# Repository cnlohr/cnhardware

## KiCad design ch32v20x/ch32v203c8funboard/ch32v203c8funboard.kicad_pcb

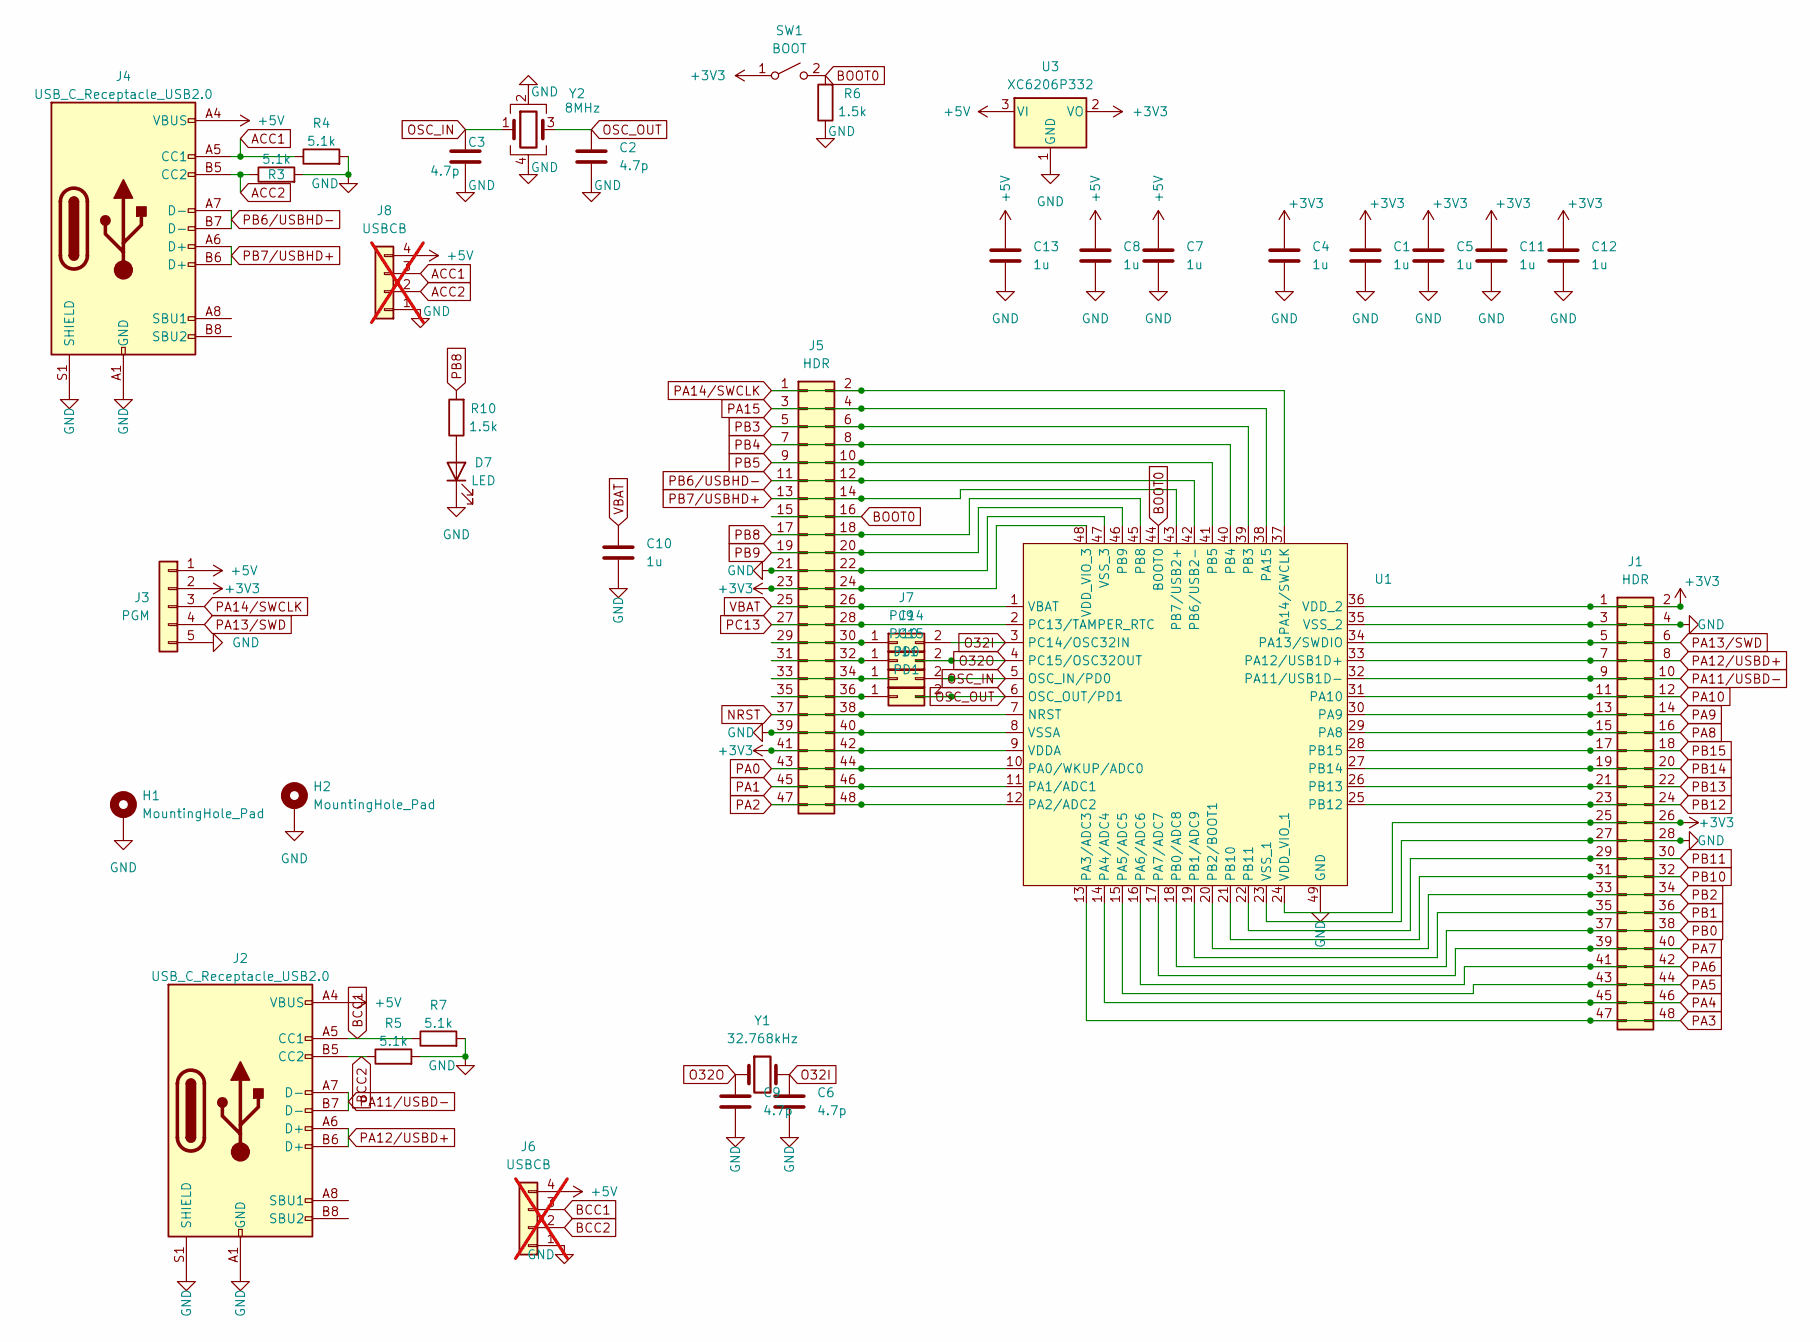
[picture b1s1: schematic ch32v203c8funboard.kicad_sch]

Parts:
C1, C4, C5, C7, C8, C10, C11, C12, C13: 1u; C_0402_1005Metric; LCSC C52923
C2, C3, C6, C9: 4.7p; C_0402_1005Metric; LCSC C325453
D7: LED; LED_0402_1005Metric; LCSC C74342
H1, H2: MountingHole_Pad; MountingHole_3.2mm_M3_DIN965_Pad
J1, J5: HDR; PinHeader_2x24_P2.54mm_Vertical; LCSC C725896
J2, J4: USB_C_Receptacle_USB2.0; USB_C_Receptacle_HRO_TYPE-C-31-M-12; LCSC C2765186
J3: PGM; PinHeader_1x05_P2.54mm_Vertical; LCSC C492404
J6, J8: USBCB; PinHeader_1x04_P2.54mm_Vertical; not fitted
J7: PC14; SolderJumper-2_P1.3mm_Open_RoundedPad1.0x1.5mm
J9: PC15; SolderJumper-2_P1.3mm_Open_RoundedPad1.0x1.5mm
J10: PD0; SolderJumper-2_P1.3mm_Open_RoundedPad1.0x1.5mm
J11: PD1; SolderJumper-2_P1.3mm_Open_RoundedPad1.0x1.5mm
R3, R4, R5, R7: 5.1k; R_0402_1005Metric; LCSC C25905
R6, R10: 1.5k; R_0402_1005Metric; LCSC C25867
SW1: BOOT; TS-1187A-B-A-B-TACTILE; LCSC C318884
U1: QFN-48-1EP_7x7mm_P0.5mm_EP5.6x5.6mm; LCSC C6407762
U3: XC6206P332; SOT-23; LCSC C5446
Y1: 32.768kHz; Crystal_SMD_3215-2Pin_3.2x1.5mm; LCSC C19076879
Y2: 8MHz; Crystal_SMD_3225-4Pin_3.2x2.5mm; LCSC C400090

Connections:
+3V3: C1.1, C4.1, C5.1, C11.1, C12.1, J1.1, J1.2, J1.25, J1.26, J3.2, J5.23, J5.24, J5.41, J5.42, SW1.1 (A), U1.9 (VDDA), U1.24 (VDD_VIO_1), U1.36 (VDD_2), U1.48 (VDD_VIO_3), U3.2 (VO)
+5V: C7.1, C8.1, C13.1, J2.A4 (VBUS), J2.A9 (VBUS), J2.B4 (VBUS), J2.B9 (VBUS), J3.1, J4.A4 (VBUS), J4.A9 (VBUS), J4.B4 (VBUS), J4.B9 (VBUS), J6.4, J8.4, U3.3 (VI)
ACC1: J4.A5 (CC1), J8.3, R4.1
ACC2: J4.B5 (CC2), J8.2, R3.1
BCC1: J2.A5 (CC1), J6.3, R7.1
BCC2: J2.B5 (CC2), J6.2, R5.1
BOOT0: J5.15, J5.16, R6.2, SW1.2 (B), U1.44 (BOOT0)
GND: C1.2, C2.2, C3.2, C4.2, C5.2, C6.2, C7.2, C8.2, C9.2, C10.2, C11.2, C12.2, C13.2, D7.1 (K), H1.1, H2.1, J1.3, J1.4, J1.27, J1.28, J2.A1 (GND), J2.A12 (GND), J2.B1 (GND), J2.B12 (GND), J2.S1 (SHIELD), J3.5, J4.A1 (GND), J4.A12 (GND), J4.B1 (GND), J4.B12 (GND), J4.S1 (SHIELD), J5.21, J5.22, J5.39, J5.40, J6.1, J8.1, R3.2, R4.2, R5.2, R6.1, R7.2, U1.8 (VSSA), U1.23 (VSS_1), U1.35 (VSS_2), U1.47 (VSS_3), U1.49 (GND), U3.1 (GND), Y2.2, Y2.4
NRST: J5.37, J5.38, U1.7 (NRST)
unnamed: D7.2 (A), R10.1
unnamed: J5.29, J5.30, J7.1
unnamed: J5.31, J5.32, J9.1
unnamed: J5.33, J5.34, J10.1
unnamed: J5.35, J5.36, J11.1
O32I: C6.1, J7.2, U1.3 (PC14/OSC32IN), Y1.2
O32O: C9.1, J9.2, U1.4 (PC15/OSC32OUT), Y1.1
OSC_IN: C3.1, J10.2, U1.5 (OSC_IN/PD0), Y2.1
OSC_OUT: C2.1, J11.2, U1.6 (OSC_OUT/PD1), Y2.3
PA0: J5.43, J5.44, U1.10 (PA0/WKUP/ADC0)
PA1: J5.45, J5.46, U1.11 (PA1/ADC1)
PA2: J5.47, J5.48, U1.12 (PA2/ADC2)
PA3: J1.47, J1.48, U1.13 (PA3/ADC3)
PA4: J1.45, J1.46, U1.14 (PA4/ADC4)
PA5: J1.43, J1.44, U1.15 (PA5/ADC5)
PA6: J1.41, J1.42, U1.16 (PA6/ADC6)
PA7: J1.39, J1.40, U1.17 (PA7/ADC7)
PA8: J1.15, J1.16, U1.29 (PA8)
PA9: J1.13, J1.14, U1.30 (PA9)
PA10: J1.11, J1.12, U1.31 (PA10)
PA11/USBD-: J1.9, J1.10, J2.A7 (D-), J2.B7 (D-), U1.32 (PA11/USB1D-)
PA12/USBD+: J1.7, J1.8, J2.A6 (D+), J2.B6 (D+), U1.33 (PA12/USB1D+)
PA13/SWD: J1.5, J1.6, J3.4, U1.34 (PA13/SWDIO)
PA14/SWCLK: J3.3, J5.1, J5.2, U1.37 (PA14/SWCLK)
PA15: J5.3, J5.4, U1.38 (PA15)
PB0: J1.37, J1.38, U1.18 (PB0/ADC8)
PB1: J1.35, J1.36, U1.19 (PB1/ADC9)
PB2: J1.33, J1.34, U1.20 (PB2/BOOT1)
PB3: J5.5, J5.6, U1.39 (PB3)
PB4: J5.7, J5.8, U1.40 (PB4)
PB5: J5.9, J5.10, U1.41 (PB5)
PB6/USBHD-: J4.A7 (D-), J4.B7 (D-), J5.11, J5.12, U1.42 (PB6/USB2-)
PB7/USBHD+: J4.A6 (D+), J4.B6 (D+), J5.13, J5.14, U1.43 (PB7/USB2+)
PB8: J5.17, J5.18, R10.2, U1.45 (PB8)
PB9: J5.19, J5.20, U1.46 (PB9)
PB10: J1.31, J1.32, U1.21 (PB10)
PB11: J1.29, J1.30, U1.22 (PB11)
PB12: J1.23, J1.24, U1.25 (PB12)
PB13: J1.21, J1.22, U1.26 (PB13)
PB14: J1.19, J1.20, U1.27 (PB14)
PB15: J1.17, J1.18, U1.28 (PB15)
PC13: J5.27, J5.28, U1.2 (PC13/TAMPER_RTC)
VBAT: C10.1, J5.25, J5.26, U1.1 (VBAT)

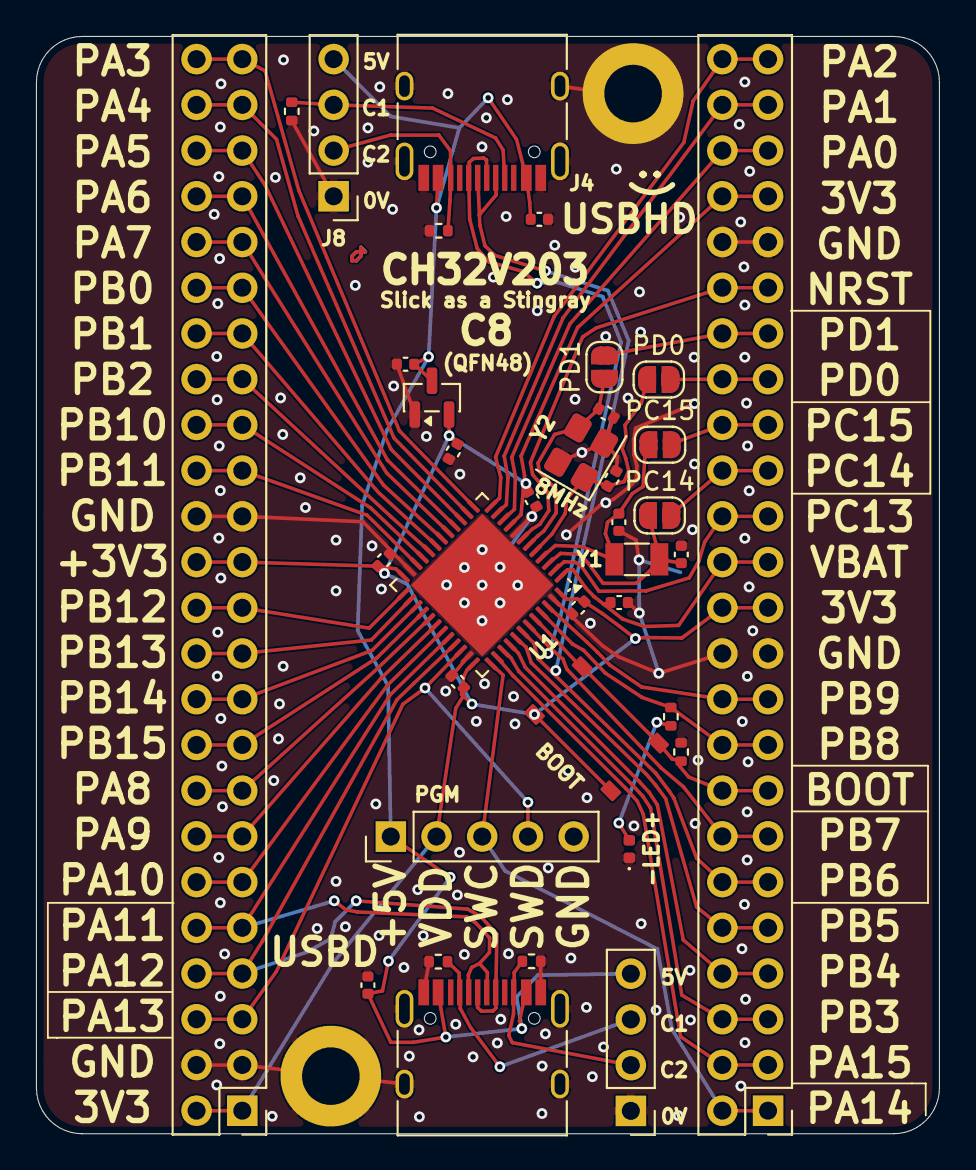
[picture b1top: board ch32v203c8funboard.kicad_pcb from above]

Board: 2 copper layers, 50.2 x 61.0 mm, 38 parts (0 on the bottom side), 52 nets.

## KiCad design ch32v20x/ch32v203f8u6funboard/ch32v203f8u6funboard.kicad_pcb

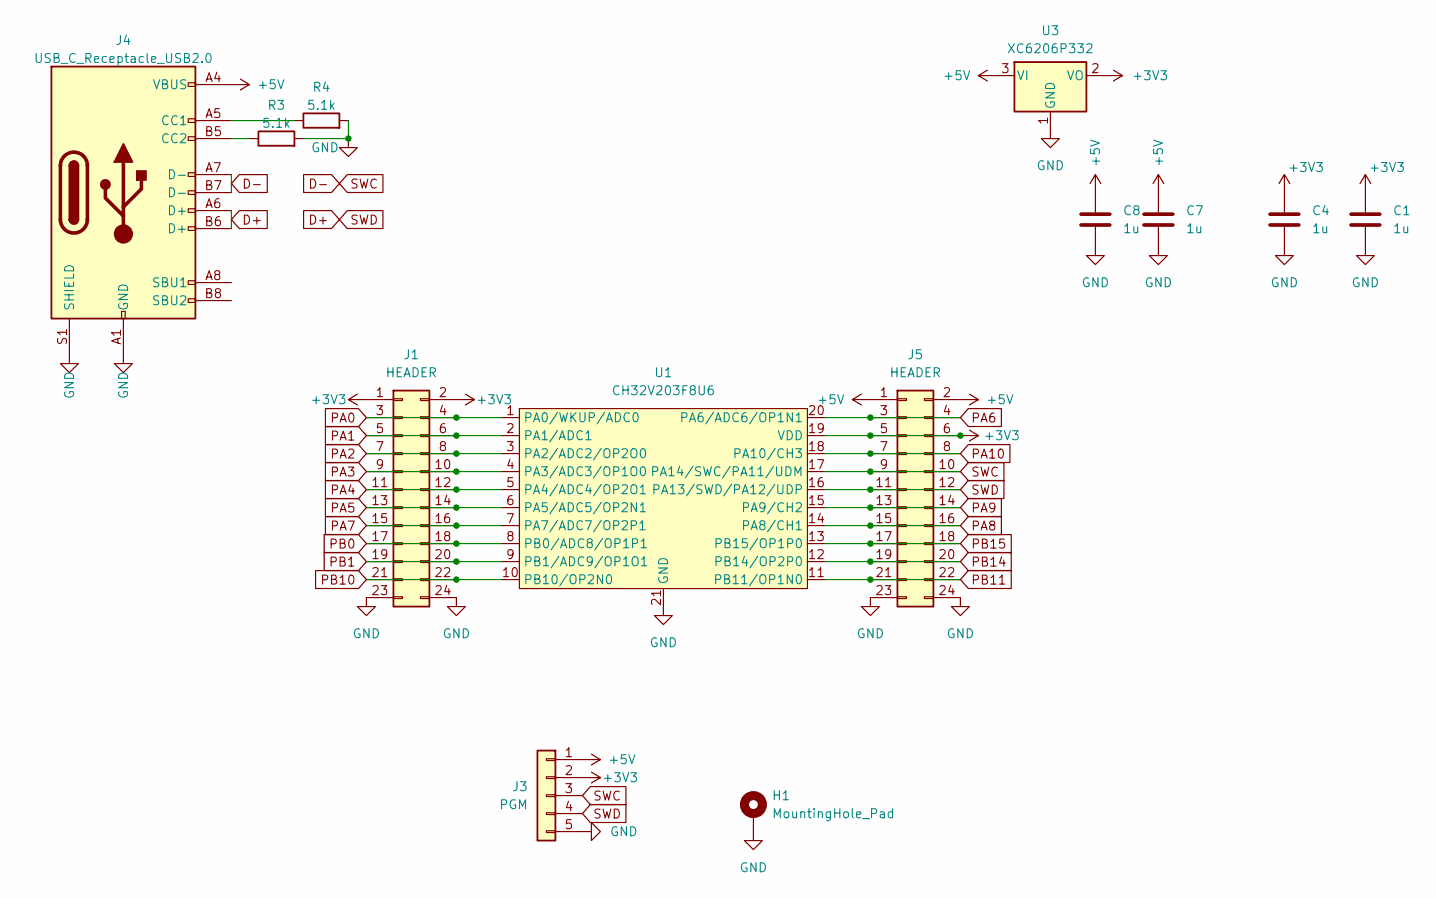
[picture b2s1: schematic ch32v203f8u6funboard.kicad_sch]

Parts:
C1, C4, C7, C8: 1u; C_0402_1005Metric; LCSC C52923
H1: MountingHole_Pad; MountingHole_3.2mm_M3_DIN965_Pad
J1, J5: HEADER; PinHeader_2x12_P2.54mm_Vertical; LCSC C492429
J3: PGM; PinHeader_1x05_P2.54mm_Vertical; LCSC C492404
J4: USB_C_Receptacle_USB2.0; USB_C_Receptacle_HRO_TYPE-C-31-M-12; LCSC C2765186
R3, R4: 5.1k; R_0402_1005Metric; LCSC C25905
U1: CH32V203F8U6; QFN-20-1EP_3x3mm_P0.4mm_EP1.65x1.65mm; LCSC C7570477
U3: XC6206P332; SOT-23; LCSC C5446

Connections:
+3V3: C1.1, C4.1, J1.1, J1.2, J3.2, J5.5, J5.6, U1.19 (VDD), U3.2 (VO)
+5V: C7.1, C8.1, J3.1, J4.A4 (VBUS), J4.A9 (VBUS), J4.B4 (VBUS), J4.B9 (VBUS), J5.1, J5.2, U3.3 (VI)
D+: J3.4, J4.A6 (D+), J4.B6 (D+), J5.11, J5.12, U1.16 (PA13/SWD/PA12/UDP)
D-: J3.3, J4.A7 (D-), J4.B7 (D-), J5.9, J5.10, U1.17 (PA14/SWC/PA11/UDM)
GND: C1.2, C4.2, C7.2, C8.2, H1.1, J1.23, J1.24, J3.5, J4.A1 (GND), J4.A12 (GND), J4.B1 (GND), J4.B12 (GND), J4.S1 (SHIELD), J5.23, J5.24, R3.2, R4.2, U1.21 (GND), U3.1 (GND)
unnamed: J4.A5 (CC1), R4.1
unnamed: J4.B5 (CC2), R3.1
PA0: J1.3, J1.4, U1.1 (PA0/WKUP/ADC0)
PA1: J1.5, J1.6, U1.2 (PA1/ADC1)
PA2: J1.7, J1.8, U1.3 (PA2/ADC2/OP2O0)
PA3: J1.9, J1.10, U1.4 (PA3/ADC3/OP1O0)
PA4: J1.11, J1.12, U1.5 (PA4/ADC4/OP2O1)
PA5: J1.13, J1.14, U1.6 (PA5/ADC5/OP2N1)
PA6: J5.3, J5.4, U1.20 (PA6/ADC6/OP1N1)
PA7: J1.15, J1.16, U1.7 (PA7/ADC7/OP2P1)
PA8: J5.15, J5.16, U1.14 (PA8/CH1)
PA9: J5.13, J5.14, U1.15 (PA9/CH2)
PA10: J5.7, J5.8, U1.18 (PA10/CH3)
PB0: J1.17, J1.18, U1.8 (PB0/ADC8/OP1P1)
PB1: J1.19, J1.20, U1.9 (PB1/ADC9/OP1O1)
PB10: J1.21, J1.22, U1.10 (PB10/OP2N0)
PB11: J5.21, J5.22, U1.11 (PB11/OP1N0)
PB14: J5.19, J5.20, U1.12 (PB14/OP2P0)
PB15: J5.17, J5.18, U1.13 (PB15/OP1P0)

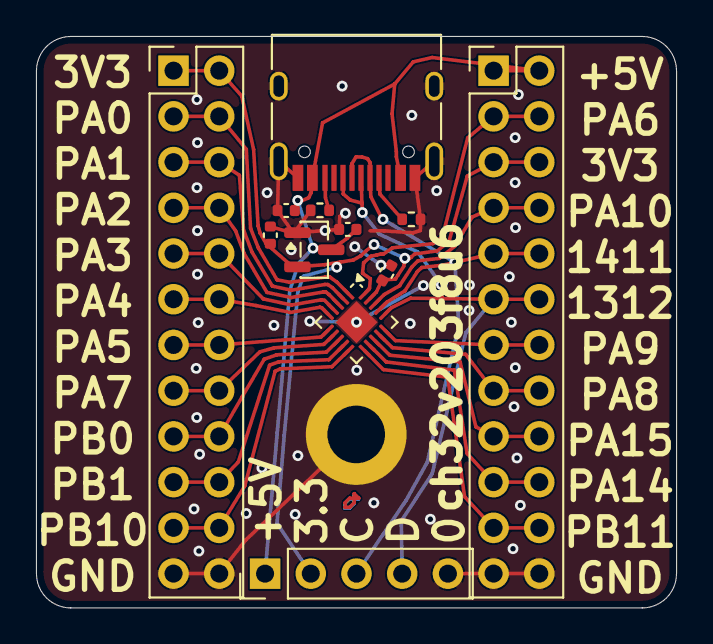
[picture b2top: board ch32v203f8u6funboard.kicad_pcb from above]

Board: 2 copper layers, 35.6 x 31.8 mm, 13 parts (0 on the bottom side), 24 nets.

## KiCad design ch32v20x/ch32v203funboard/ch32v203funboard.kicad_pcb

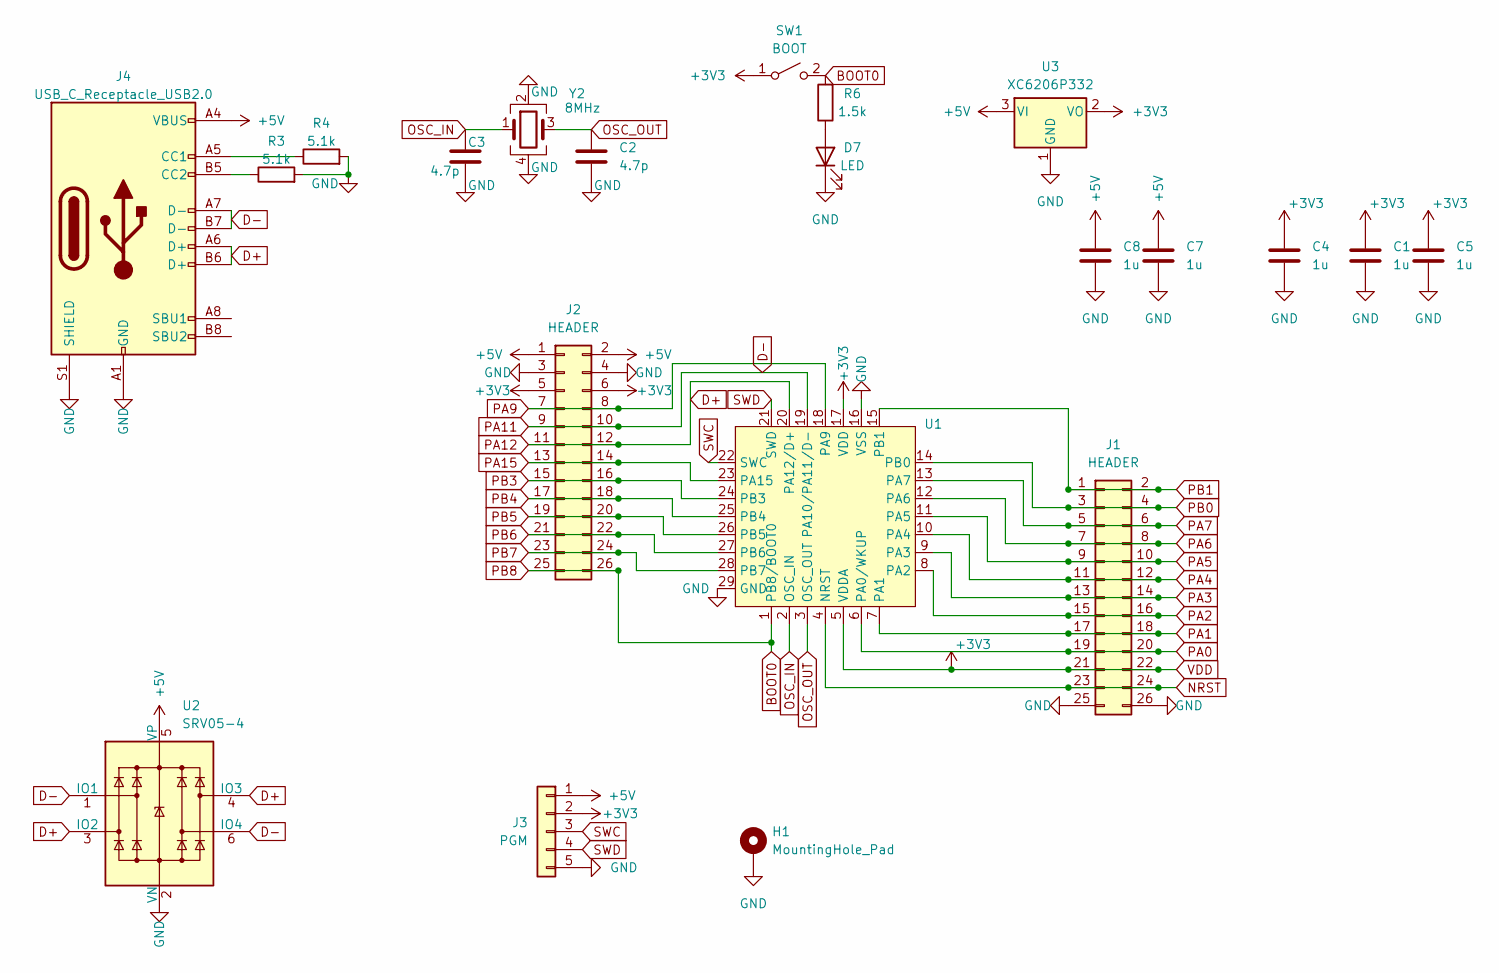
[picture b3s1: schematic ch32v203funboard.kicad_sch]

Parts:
C1, C4, C5, C7, C8: 1u; C_0402_1005Metric; LCSC C52923
C2, C3: 4.7p; C_0402_1005Metric; LCSC C325453
D7: LED; LED_0402_1005Metric; LCSC C74342
H1: MountingHole_Pad; MountingHole_3.2mm_M3_DIN965_Pad
J1, J2: HEADER; PinHeader_2x13_P2.54mm_Vertical; LCSC C358701
J3: PGM; PinHeader_1x05_P2.54mm_Vertical; LCSC C492404
J4: USB_C_Receptacle_USB2.0; USB_C_Receptacle_HRO_TYPE-C-31-M-12; LCSC C2765186
R3, R4: 5.1k; R_0402_1005Metric; LCSC C25905
R6: 1.5k; R_0402_1005Metric; LCSC C25867
SW1: BOOT; TS-1187A-B-A-B-TACTILE; LCSC C318884
U1: QFN-28-1EP_4x4mm_P0.4mm_EP2.3x2.3mm; LCSC C5142280
U2: SRV05-4; SOT-23-6; LCSC C2836319
U3: XC6206P332; SOT-23; LCSC C5446
Y2: 8MHz; Crystal_SMD_3225-4Pin_3.2x2.5mm; LCSC C400090

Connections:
+5V: C7.1, C8.1, J2.1, J2.2, J3.1, J4.A4 (VBUS), J4.A9 (VBUS), J4.B4 (VBUS), J4.B9 (VBUS), U2.5 (VP), U3.3 (VI)
BOOT0: J2.25, J2.26, R6.2, SW1.2 (B), U1.1 (PB8/BOOT0)
D+: J2.11, J2.12, J4.A6 (D+), J4.B6 (D+), U1.20 (PA12/D+), U2.3 (IO2), U2.4 (IO3)
D-: J2.9, J2.10, J4.A7 (D-), J4.B7 (D-), U1.19 (PA10/PA11/D-), U2.1 (IO1), U2.6 (IO4)
GND: C1.2, C2.2, C3.2, C4.2, C5.2, C7.2, C8.2, D7.1 (K), H1.1, J1.25, J1.26, J2.3, J2.4, J3.5, J4.A1 (GND), J4.A12 (GND), J4.B1 (GND), J4.B12 (GND), J4.S1 (SHIELD), R3.2, R4.2, U1.16 (VSS), U1.29 (GND), U2.2 (VN), U3.1 (GND), Y2.2, Y2.4
NRST: J1.23, J1.24, U1.4 (NRST)
unnamed: D7.2 (A), R6.1
unnamed: J4.A5 (CC1), R4.1
unnamed: J4.B5 (CC2), R3.1
OSC_IN: C3.1, U1.2 (OSC_IN), Y2.1
OSC_OUT: C2.1, U1.3 (OSC_OUT), Y2.3
PA0: J1.19, J1.20, U1.6 (PA0/WKUP)
PA1: J1.17, J1.18, U1.7 (PA1)
PA2: J1.15, J1.16, U1.8 (PA2)
PA3: J1.13, J1.14, U1.9 (PA3)
PA4: J1.11, J1.12, U1.10 (PA4)
PA5: J1.9, J1.10, U1.11 (PA5)
PA6: J1.7, J1.8, U1.12 (PA6)
PA7: J1.5, J1.6, U1.13 (PA7)
PA9: J2.7, J2.8, U1.18 (PA9)
PA15: J2.13, J2.14, U1.23 (PA15)
PB0: J1.3, J1.4, U1.14 (PB0)
PB1: J1.1, J1.2, U1.15 (PB1)
PB3: J2.15, J2.16, U1.24 (PB3)
PB4: J2.17, J2.18, U1.25 (PB4)
PB5: J2.19, J2.20, U1.26 (PB5)
PB6: J2.21, J2.22, U1.27 (PB6)
PB7: J2.23, J2.24, U1.28 (PB7)
SWC: J3.3, U1.22 (SWC)
SWD: J3.4, U1.21 (SWD)
VDD: C1.1, C4.1, C5.1, J1.21, J1.22, J2.5, J2.6, J3.2, SW1.1 (A), U1.5 (VDDA), U1.17 (VDD), U3.2 (VO)

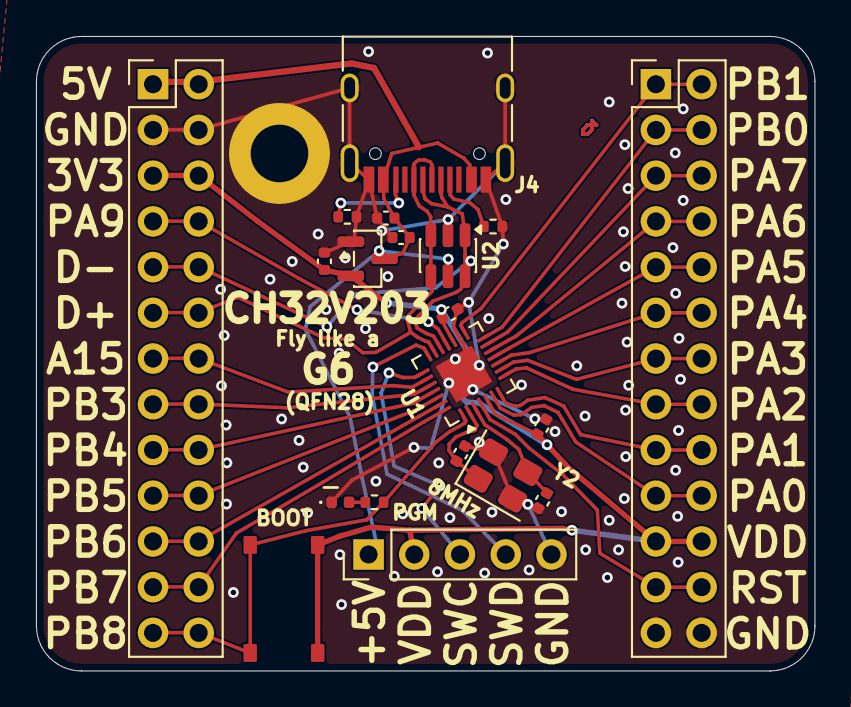
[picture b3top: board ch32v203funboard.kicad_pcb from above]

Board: 2 copper layers, 43.2 x 35.2 mm, 21 parts (0 on the bottom side), 31 nets.

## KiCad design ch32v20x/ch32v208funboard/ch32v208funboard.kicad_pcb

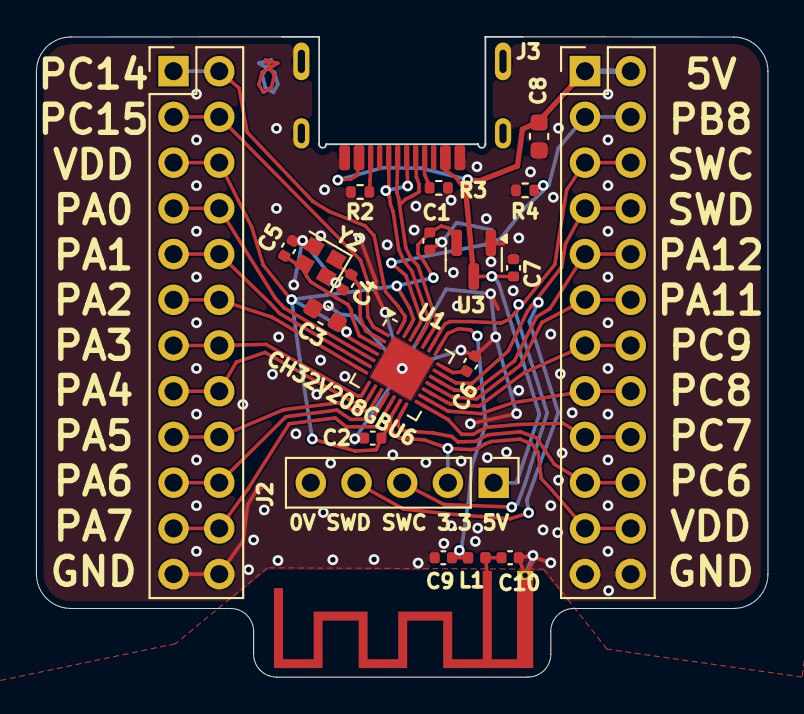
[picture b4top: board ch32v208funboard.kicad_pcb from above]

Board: 2 copper layers, 40.6 x 35.6 mm, 22 parts (0 on the bottom side), 31 nets.

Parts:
A1: PRO-OB-440; Texas_SWRA117D_2.4GHz_Right
C1, C2, C6, C7: 1u; C_0402_1005Metric
C3, C8: 10u; C_0603_1608Metric
C4, C5: 4.7p; C_0402_1005Metric
C9, C10: 1p8; C_0402_1005Metric
J1, J4: HDR; PinHeader_2x12_P2.54mm_Vertical
J2: PGM; PinHeader_1x05_P2.54mm_Vertical
J3: USB_C_Receptacle_USB2.0; USB_C_TIGHT_IN_BOARD_161N-4BC21665
L1: 1n8; L_0402_1005Metric
R2, R3, R4: 5.1k; R_0402_1005Metric
U1: CH32V208GBU6; QFN-28-1EP_4x4mm_P0.4mm_EP2.6x2.6mm
U3: XC6206P332; SOT-23
Y2: 32MHz; Crystal_SMD_2016-4Pin_2.0x1.6mm

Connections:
+5V: C7.1, C8.1, J2.1, J3.A4 (VBUS), J3.A9 (VBUS), J3.B4 (VBUS), J3.B9 (VBUS), J4.1, J4.2, U3.3 (VI)
CC1: J3.A5 (CC1), R3.1
CC2: J3.B5 (CC2), R2.1
D+: J3.A6 (D+), J3.B6 (D+), U1.25 (PB7/U2+)
D-: J3.A7 (D-), J3.B7 (D-), U1.24 (PB6/U2-)
GND: A1.2, C1.2, C2.2, C3.2, C4.2, C5.2, C6.2, C7.2, C8.2, C9.2, C10.2, J1.23, J1.24, J2.5, J3.A1 (GND), J3.A12 (GND), J3.B1 (GND), J3.B12 (GND), J3.S1 (SHIELD), J4.23, J4.24, R2.2, R3.2, R4.2, U1.29 (GND), U3.1 (GND), Y2.2, Y2.4
unnamed: A1.1, C10.1, L1.2
unnamed: J1.1, J1.2, U1.28 (PC14)
unnamed: J1.3, J1.4, U1.1 (PC15)
unnamed: J1.7, J1.8, U1.5 (PA0)
unnamed: J1.9, J1.10, U1.6 (PA1)
unnamed: J1.11, J1.12, U1.7 (PA2)
unnamed: J1.13, J1.14, U1.8 (PA3)
unnamed: J1.15, J1.16, U1.9 (PA4)
unnamed: J1.17, J1.18, U1.10 (PA5)
unnamed: J1.19, J1.20, U1.11 (PA6)
unnamed: J1.21, J1.22, U1.12 (PA7)
unnamed: J4.3, J4.4, R4.1, U1.26 (PB8/B0)
unnamed: J4.9, J4.10, U1.19 (PA12/U1+)
unnamed: J4.11, J4.12, U1.18 (PA11/USB1DM)
unnamed: J4.13, J4.14, U1.17 (PC9)
unnamed: J4.15, J4.16, U1.16 (PC8)
unnamed: J4.17, J4.18, U1.15 (PC7)
unnamed: J4.19, J4.20, U1.14 (PC6)
unnamed: C9.1, L1.1, U1.22 (ANT)
unnamed: C6.1, U1.21 (VINTA)
OSC_IN: C4.1, U1.2 (OSC_IN), Y2.1
OSC_OUT: C5.1, U1.3 (OSC_OUT), Y2.3
PA13/SWD: J2.4, J4.7, J4.8, U1.20 (SWD)
PA14/SWCLK: J2.3, J4.5, J4.6, U1.23 (SWC)
VDD: C1.1, C2.1, C3.1, J1.5, J1.6, J2.2, J4.21, J4.22, U1.4 (VDDA), U1.13 (VDD_VIO), U1.27 (VDD), U3.2 (VO)

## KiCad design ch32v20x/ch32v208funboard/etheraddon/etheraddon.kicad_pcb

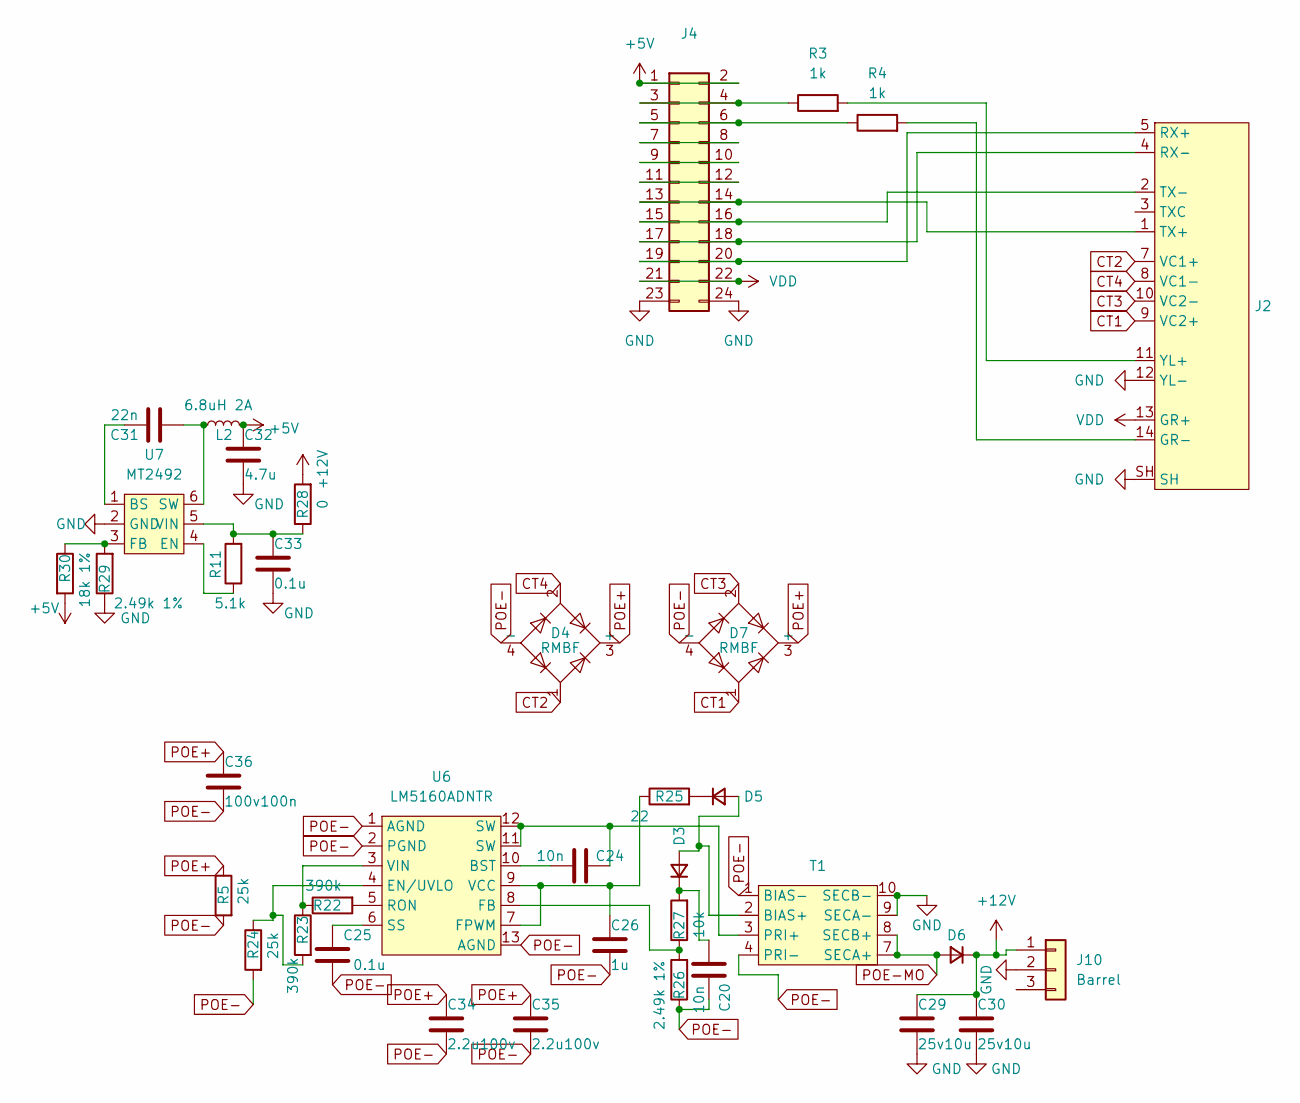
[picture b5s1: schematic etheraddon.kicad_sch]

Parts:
C20, C24: 10n; C_0402_1005Metric; LCSC C15195
C25, C33: 0.1u; C_0402_1005Metric; LCSC C1525
C26: 1u; C_0402_1005Metric; LCSC C52923
C29, C30: 25v10u; C_0805_2012Metric; LCSC C15850
C31: 22n; C_0402_1005Metric; LCSC C1532
C32: 4.7u; C_0402_1005Metric; LCSC C368809
C34, C35: 2.2u100v; C_1206_3216Metric; LCSC C920964
C36: 100v100n; C_0805_2012Metric; LCSC C28233
D3, D5: D_SOD-323; LCSC C2128
D4, D7: RMBF; TO-269AA; LCSC C7450442
D6: D_SOD-123F; LCSC C122863
J2: RJ45_HANRUN_HR871150C; LCSC C19724786
J4: HDR; PinSocket_2x12_P2.54mm_Vertical; LCSC C34413557
J10: Barrel; BarrelJack_GCT_DCJ200-10-A_Horizontal; LCSC C136744
L2: 6.8uH 2A; L_Taiyo-Yuden_MD-4040; LCSC C97036
R3, R4: 1k; R_0402_1005Metric; LCSC C11702
R5, R24: 25k; R_0402_1005Metric; LCSC C25874
R11: 5.1k; R_0402_1005Metric; LCSC C258132
R22, R23: 390k; R_0402_1005Metric; LCSC C162853
R25: 22; R_0402_1005Metric; LCSC C25092
R26, R29: 2.49k 1%; R_0402_1005Metric; LCSC C145071
R27: 10k; R_0402_1005Metric; LCSC C25744
R28: 0; R_0402_1005Metric; LCSC C17168
R30: 18k 1%; R_0402_1005Metric; LCSC C138044
T1: TNK-TSA021-POE-TRANSFORMER; LCSC C55680
U6: LM5160ADNTR; DFN-12-1EP_4x4mm_P0.5mm_EP2.66x3.38mm; LCSC C473375
U7: MT2492; SOT-23-6; LCSC C89358

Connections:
+5V: C32.1, J4.1, J4.2, L2.2, R30.2
+12V: C29.1, C30.1, D6.1 (K), J10.1, R28.2
CT1: D7.1, J2.9 (VC2+)
CT2: D4.1, J2.7 (VC1+)
CT3: D7.2, J2.10 (VC2-)
CT4: D4.2, J2.8 (VC1-)
GND: C29.2, C30.2, C32.2, C33.2, J2.12 (YL-), J2.SH, J4.23, J4.24, J10.2, R29.1, T1.9 (SECA-), T1.10 (SECB-), U7.2 (GND)
unnamed: D3.2 (A), D5.2 (A), T1.2 (BIAS+)
unnamed: C20.2, D3.1 (K), R27.2
unnamed: D5.1 (K), R25.2
unnamed: J2.14 (GR-), R4.2
unnamed: J2.5 (RX+), J4.19, J4.20
unnamed: J2.4 (RX-), J4.17, J4.18
unnamed: J2.1 (TX+), J4.13, J4.14
unnamed: J2.2 (TX-), J4.15, J4.16
unnamed: J2.11 (YL+), R3.2
unnamed: J4.3, J4.4, R3.1
unnamed: J4.5, J4.6, R4.1
unnamed: J4.7, J4.8
unnamed: J4.9, J4.10
unnamed: J4.11, J4.12
unnamed: C24.2, T1.3 (PRI+), U6.11 (SW), U6.12 (SW)
unnamed: C24.1, U6.10 (BST)
unnamed: R23.2, R24.1, U6.4 (EN/UVLO)
unnamed: R26.2, R27.1, U6.8 (FB)
unnamed: C26.1, R25.1, U6.7 (FPWM), U6.9 (VCC)
unnamed: R22.2, U6.5 (RON)
unnamed: C25.1, U6.6 (SS)
unnamed: R22.1, R23.1, U6.3 (VIN)
unnamed: C31.1, U7.1 (BS)
unnamed: R11.1, U7.4 (EN)
unnamed: R29.2, R30.1, U7.3 (FB)
unnamed: C31.2, L2.1, U7.6 (SW)
unnamed: C33.1, R11.2, R28.1, U7.5 (VIN)
POE+: C34.1, C35.1, C36.1, D4.3 (+), D7.3 (+), R5.1
POE-: C20.1, C25.2, C26.2, C34.2, C35.2, C36.2, D4.4 (-), D7.4 (-), R5.2, R24.2, R26.1, T1.1 (BIAS-), T1.4 (PRI-), U6.1 (AGND), U6.2 (PGND), U6.13 (AGND)
POE-MO: D6.2 (A), T1.7 (SECA+), T1.8 (SECB+)
VDD: J2.13 (GR+), J4.21, J4.22

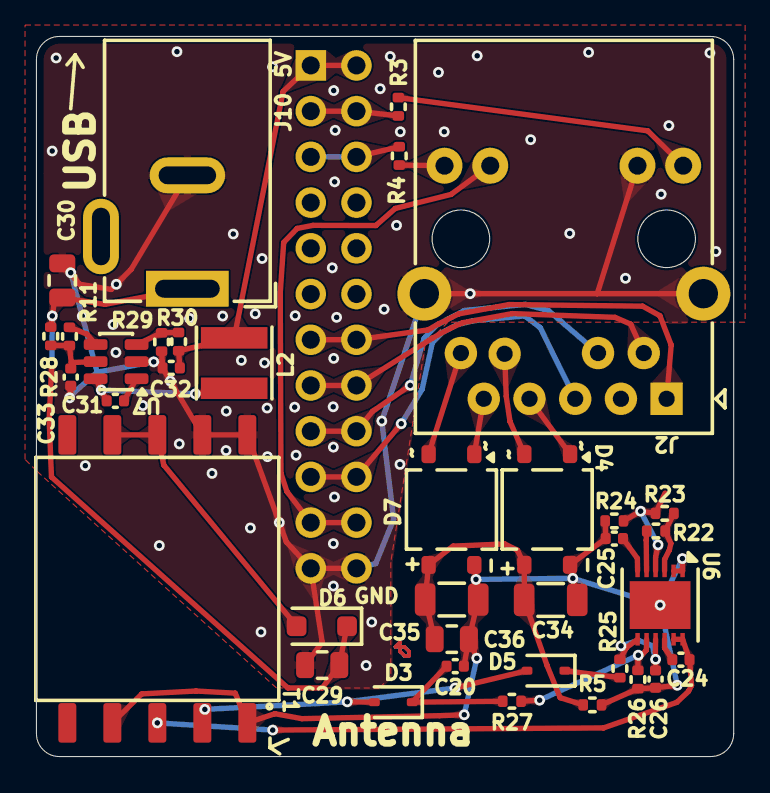
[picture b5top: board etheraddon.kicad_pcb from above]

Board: 2 copper layers, 38.7 x 40.0 mm, 37 parts (1 on the bottom side), 38 nets.
